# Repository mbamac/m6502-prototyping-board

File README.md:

# m6502-prototyping-board

Prototyping board for 65c02 processor. Made with Eagle PCB 9.4.1

## License

[Creative Commons Attribution-NonCommercial-ShareAlike 4.0 International (CC BY-NC-SA 4.0)](https://creativecommons.org/licenses/by-nc-sa/4.0/)

## BOM
required:
* microprocessor W65C02S6TP - 1pcs
* static RAM CY62256LL-PC - 2 pcs
* eeprom AT28C64 - 1pcs
* quartz oscillator 1MHz-8MHz - 1pcs
* smd resistor 3.3K 1206 - 5pcs
* capacitor 100nF 0805 - 4pcs
* goldpins

optional:
* single inverter 74AHC1G04 in SOT23-5 package - 1pcs

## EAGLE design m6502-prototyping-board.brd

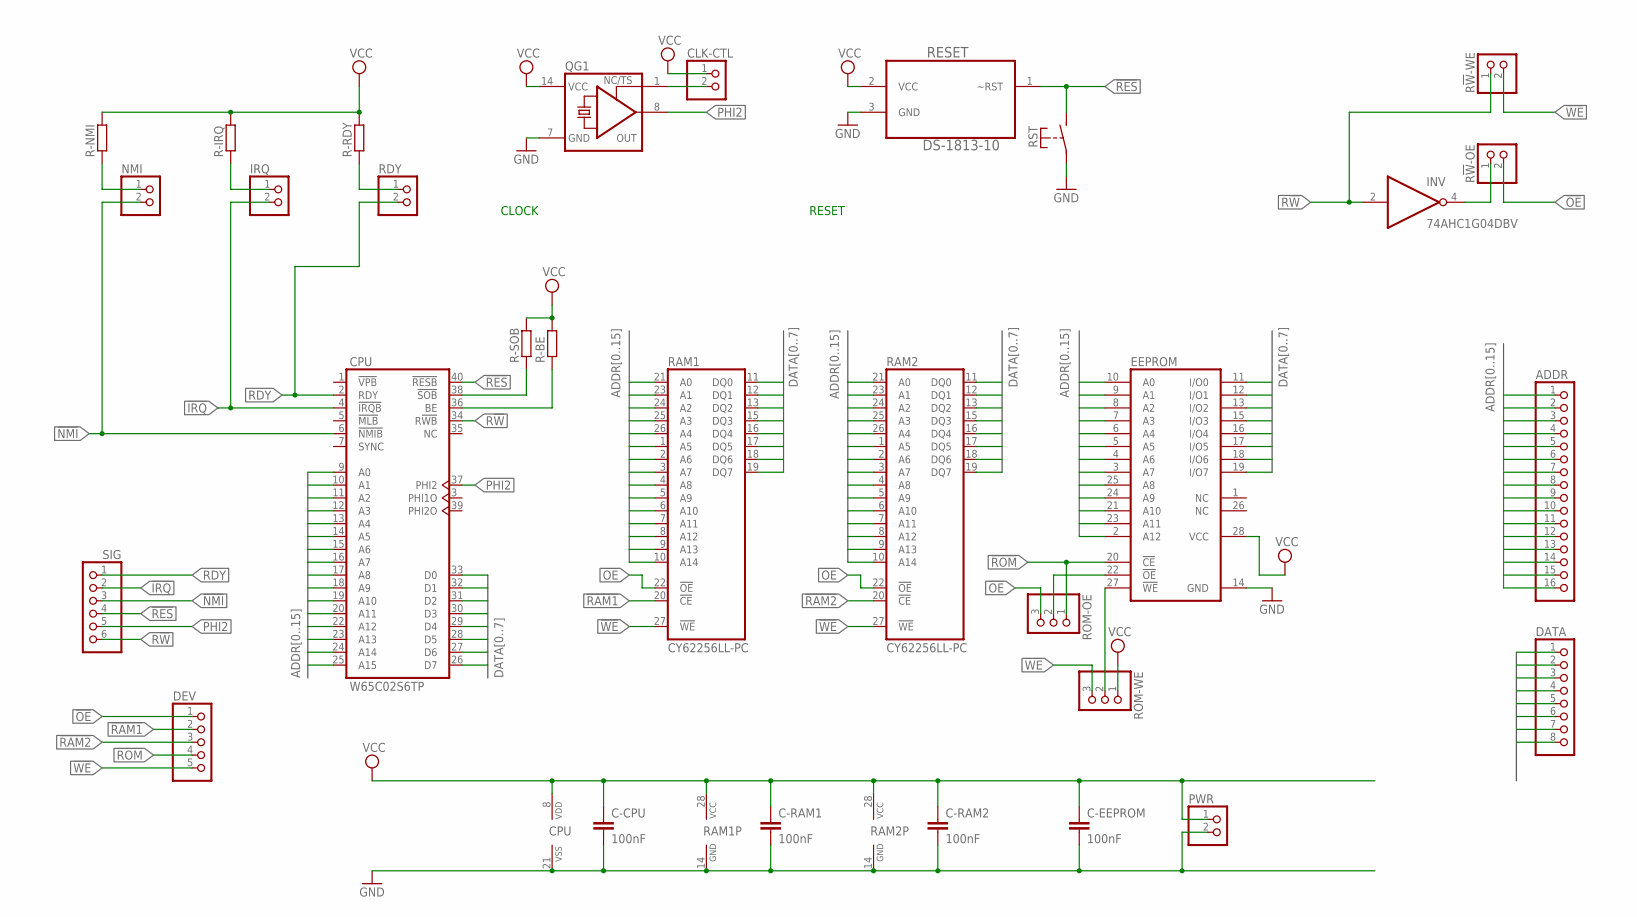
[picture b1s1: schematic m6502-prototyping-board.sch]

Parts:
ADDR: PINHD-1X16; 1X16
C-CPU: 100nF; C0805
C-EEPROM: 100nF; C0805
C-RAM1, C-RAM2: 100nF; C0805
CLK-CTL: PINHD-1X2; 1X02
CPU: W65C02S6TP; DIL40
DATA: PINHD-1X8; 1X08
DEV: PINHD-1X5; 1X05
EEPROM: 28C64C; DIL28-6
INV: 74AHC1G04DBV; SOT23-5
IRQ: PINHD-1X2; 1X02
NMI: PINHD-1X2; 1X02
PWR: PINHD-1X2; 1X02
QG1: XO-14; DIL14S
R!W!-OE: PINHD-1X2; 1X02
R!W!-WE: PINHD-1X2; 1X02
R-BE: R-EU_M1206; M1206
R-IRQ: R-EU_M1206; M1206
R-NMI: R-EU_M1206; M1206
R-RDY: R-EU_M1206; M1206
R-SOB: R-EU_M1206; M1206
RAM1, RAM2: CY62256LL-PC; DIL28-6
RDY: PINHD-1X2; 1X02
RESET: DS-1813-10; TO-92
ROM-OE: PINHD-1X3; 1X03
ROM-WE: PINHD-1X3; 1X03
RST: FSM
SIG: PINHD-1X6; 1X06

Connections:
!IRQ: CPU.4 (!IRQB), IRQ.2, SIG.2
!NMI: CPU.6 (!NMIB), NMI.2, SIG.3
!OE: DEV.1, R!W!-OE.2, RAM1.22 (!OE), RAM2.22 (!OE), ROM-OE.3
!RAM1: DEV.2, RAM1.20 (!CE)
!RAM2: DEV.3, RAM2.20 (!CE)
!RES: CPU.40 (!RESB), RESET.1 (~RST), RST.P$2 (S), SIG.4
!ROM: DEV.4, EEPROM.20 (!CE), ROM-OE.1
!WE: DEV.5, R!W!-WE.2, RAM1.27 (!WE), RAM2.27 (!WE), ROM-WE.3
ADDR0: ADDR.1, CPU.9 (A0), EEPROM.10 (A0), RAM1.10 (A14), RAM2.10 (A14)
ADDR1: ADDR.2, CPU.10 (A1), EEPROM.9 (A1), RAM1.9 (A13), RAM2.9 (A13)
ADDR2: ADDR.3, CPU.11 (A2), EEPROM.8 (A2), RAM1.8 (A12), RAM2.8 (A12)
ADDR3: ADDR.4, CPU.12 (A3), EEPROM.7 (A3), RAM1.7 (A11), RAM2.7 (A11)
ADDR4: ADDR.5, CPU.13 (A4), EEPROM.6 (A4), RAM1.6 (A10), RAM2.6 (A10)
ADDR5: ADDR.6, CPU.14 (A5), EEPROM.5 (A5), RAM1.5 (A9), RAM2.5 (A9)
ADDR6: ADDR.7, CPU.15 (A6), EEPROM.4 (A6), RAM1.4 (A8), RAM2.4 (A8)
ADDR7: ADDR.8, CPU.16 (A7), EEPROM.3 (A7), RAM1.3 (A7), RAM2.3 (A7)
ADDR8: ADDR.9, CPU.17 (A8), EEPROM.25 (A8), RAM1.25 (A3), RAM2.25 (A3)
ADDR9: ADDR.10, CPU.18 (A9), EEPROM.24 (A9), RAM1.24 (A2), RAM2.24 (A2)
ADDR10: ADDR.11, CPU.19 (A10), EEPROM.21 (A10), RAM1.21 (A0), RAM2.21 (A0)
ADDR11: ADDR.12, CPU.20 (A11), EEPROM.23 (A11), RAM1.23 (A1), RAM2.23 (A1)
ADDR12: ADDR.13, CPU.22 (A12), EEPROM.2 (A12), RAM1.2 (A6), RAM2.2 (A6)
ADDR13: ADDR.14, CPU.23 (A13), RAM1.26 (A4), RAM2.26 (A4)
ADDR14: ADDR.15, CPU.24 (A14), RAM1.1 (A5), RAM2.1 (A5)
ADDR15: ADDR.16, CPU.25 (A15)
DATA0: CPU.33 (D0), DATA.1, EEPROM.11 (I/O0), RAM1.11 (DQ0), RAM2.11 (DQ0)
DATA1: CPU.32 (D1), DATA.2, EEPROM.12 (I/O1), RAM1.12 (DQ1), RAM2.12 (DQ1)
DATA2: CPU.31 (D2), DATA.3, EEPROM.13 (I/O2), RAM1.13 (DQ2), RAM2.13 (DQ2)
DATA3: CPU.30 (D3), DATA.4, EEPROM.15 (I/O3), RAM1.15 (DQ3), RAM2.15 (DQ3)
DATA4: CPU.29 (D4), DATA.5, EEPROM.16 (I/O4), RAM1.16 (DQ4), RAM2.16 (DQ4)
DATA5: CPU.28 (D5), DATA.6, EEPROM.17 (I/O5), RAM1.17 (DQ5), RAM2.17 (DQ5)
DATA6: CPU.27 (D6), DATA.7, EEPROM.18 (I/O6), RAM1.18 (DQ6), RAM2.18 (DQ6)
DATA7: CPU.26 (D7), DATA.8, EEPROM.19 (I/O7), RAM1.19 (DQ7), RAM2.19 (DQ7)
GND: C-CPU.2, C-EEPROM.2, C-RAM1.2, C-RAM2.2, CPU.21 (VSS), EEPROM.14 (GND), INV.3 (GND), PWR.2, QG1.7 (GND), RAM1.14 (GND), RAM2.14 (GND), RESET.3 (GND), RST.P$1
unnamed: NMI.1, R-NMI.1
unnamed: IRQ.1, R-IRQ.1
unnamed: EEPROM.27 (!WE), ROM-WE.2
unnamed: CPU.38 (!SOB), R-SOB.1
unnamed: EEPROM.22 (!OE), ROM-OE.2
unnamed: CPU.36 (BE), R-BE.1
unnamed: R-RDY.1, RDY.1
unnamed: CLK-CTL.2, QG1.1 (TS)
unnamed: INV.4 (O), R!W!-OE.1
PHI2: CPU.37 (PHI2), QG1.8 (OUT), SIG.5
R!W: CPU.34 (R!WB), INV.2 (I), R!W!-WE.1, SIG.6
RDY: CPU.2 (RDY), RDY.2, SIG.1
VCC: C-CPU.1, C-EEPROM.1, C-RAM1.1, C-RAM2.1, CLK-CTL.1, CPU.8 (VDD), EEPROM.28 (VCC), INV.5 (VCC), PWR.1, QG1.14 (VCC), R-BE.2, R-IRQ.2, R-NMI.2, R-RDY.2, R-SOB.2, RAM1.28 (VCC), RAM2.28 (VCC), RESET.2 (VCC), ROM-WE.1

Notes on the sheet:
CLOCK
RESET

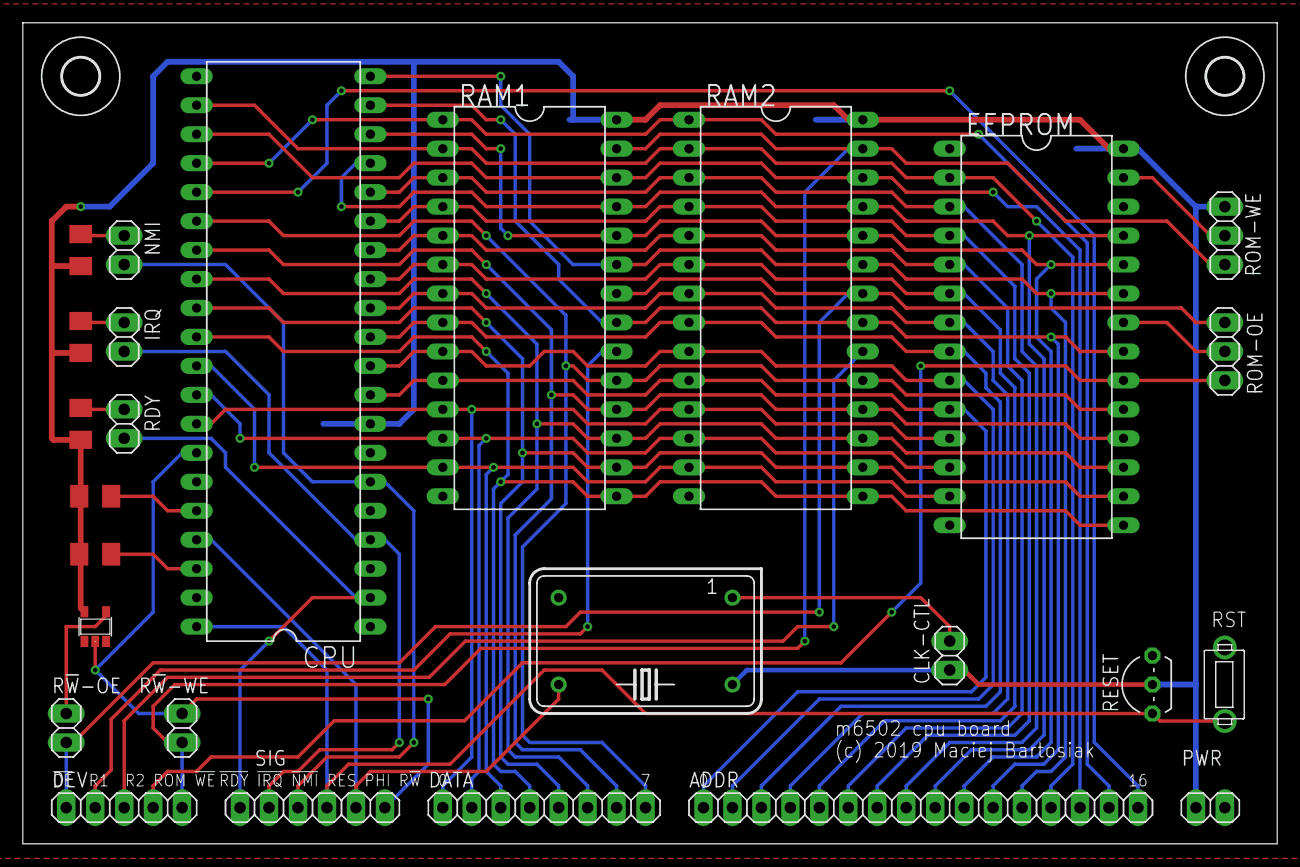
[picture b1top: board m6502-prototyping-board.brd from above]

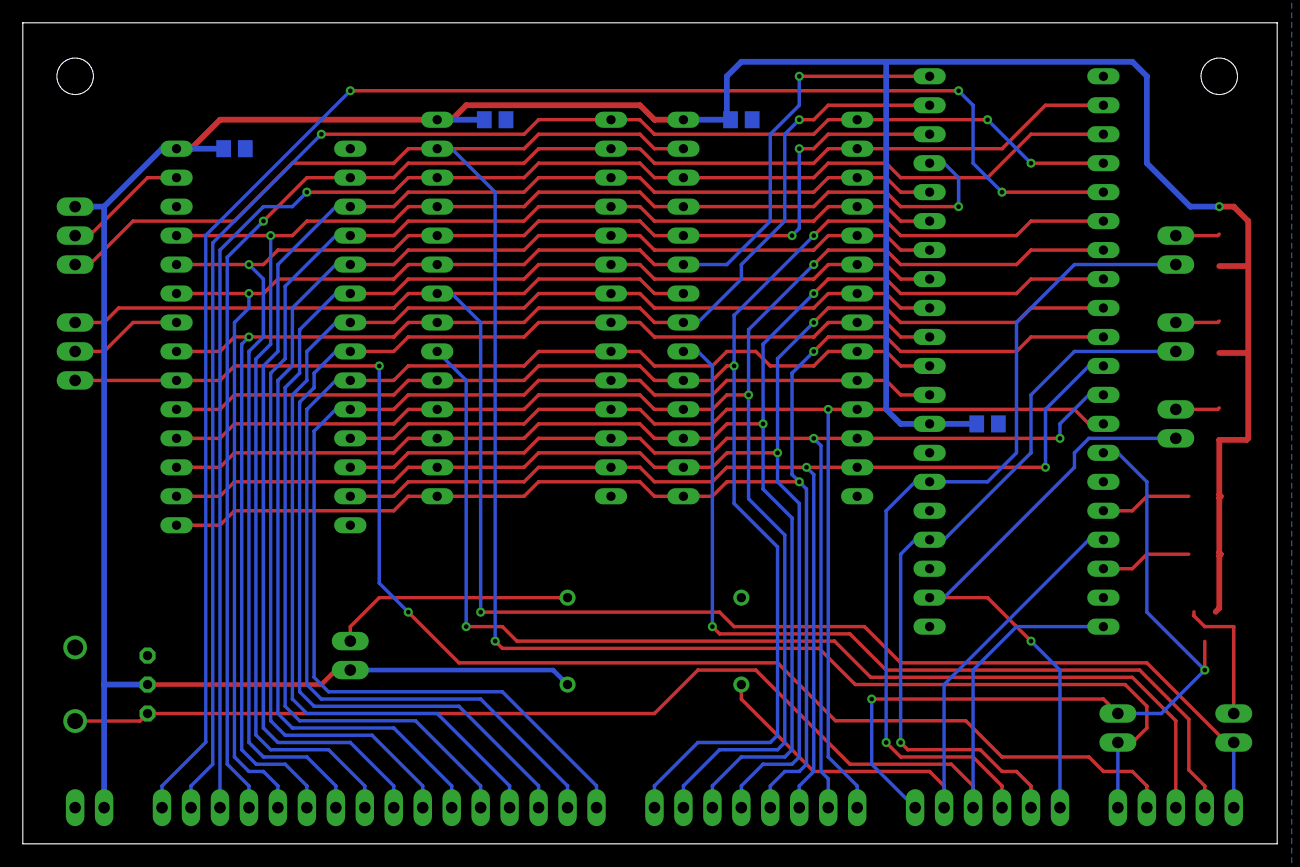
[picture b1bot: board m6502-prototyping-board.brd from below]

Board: 2 copper layers, 110.0 x 72.0 mm, 32 parts (4 on the bottom side), 46 nets.

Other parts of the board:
U$1, U$2: 3,2

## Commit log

2019-07-19 first
2019-07-24 Update README.md
    added BOM
2019-07-29 added .gitigore to skip eagle backup files
2019-07-29 removed RDY connection to eeprom
2019-08-06 exclude some files from repostiory
2019-09-07 Added license section to README.md

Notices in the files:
m6502-prototyping-board.brd:
(c) 2019 Maciej Bartosiak
